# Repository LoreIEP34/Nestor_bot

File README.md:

# Nestor_bot
## Descripción:
Un robot controlado con esp32, que recibe señales bluetooth de un control de Playstation3 (Ps3), movilizado con motores dc que estan direccionados por un puente h, con 2 brazos hechos con servomotores que a traves de una garra improvisada puede sujetar objetos livianos y con un esp32 cam puede transmitir video a traves de wifi para poder ver lo a lo mismo que el robot ve.
##contenido del repositorio:
- /code: en esta carpeta  se puede encontrar el codigo para el funcionamiento del robot, en el cual se encuentra la deteccion del control Ps3 y la logica para el envio correcto de señales. El codigo fue diseñado y utilizado en arduino ide con lenguaje c.
- /hardware: en esta carpeta se podra encontrar el esquema y diseño de la pcb del robot hecho en la herraienta de diseño Kicad, en la version 8.0.
---
## Notas:
- El codigo para el funcionamiento del esp32 cam se puede conseguir facilmente en los ejemplos de esp32 en el arduino ide. Tambien se podria crear un codigo propio del funcionamiento para customizar el proyecto.
- Para poder tener mayor flexibilidad en el movimiento de la camara en la posicion mas conveninete simplemente conectamos de manera directa la placa principal con el esp32 cam con cables para alimentarlo.
- Para el ensamblaje y la presentacion final en este caso solo utilizamos carton prenzado con tornillos y poco mas, por esa razon no hay un diseño 3d del proyecto.
---
Este proyecto fue realizado como trabajo de aprendisaje escolar en la Tecnina N5 de Temperley, tambien conocida como "2 de abril" en Buenos Aires Argentina.

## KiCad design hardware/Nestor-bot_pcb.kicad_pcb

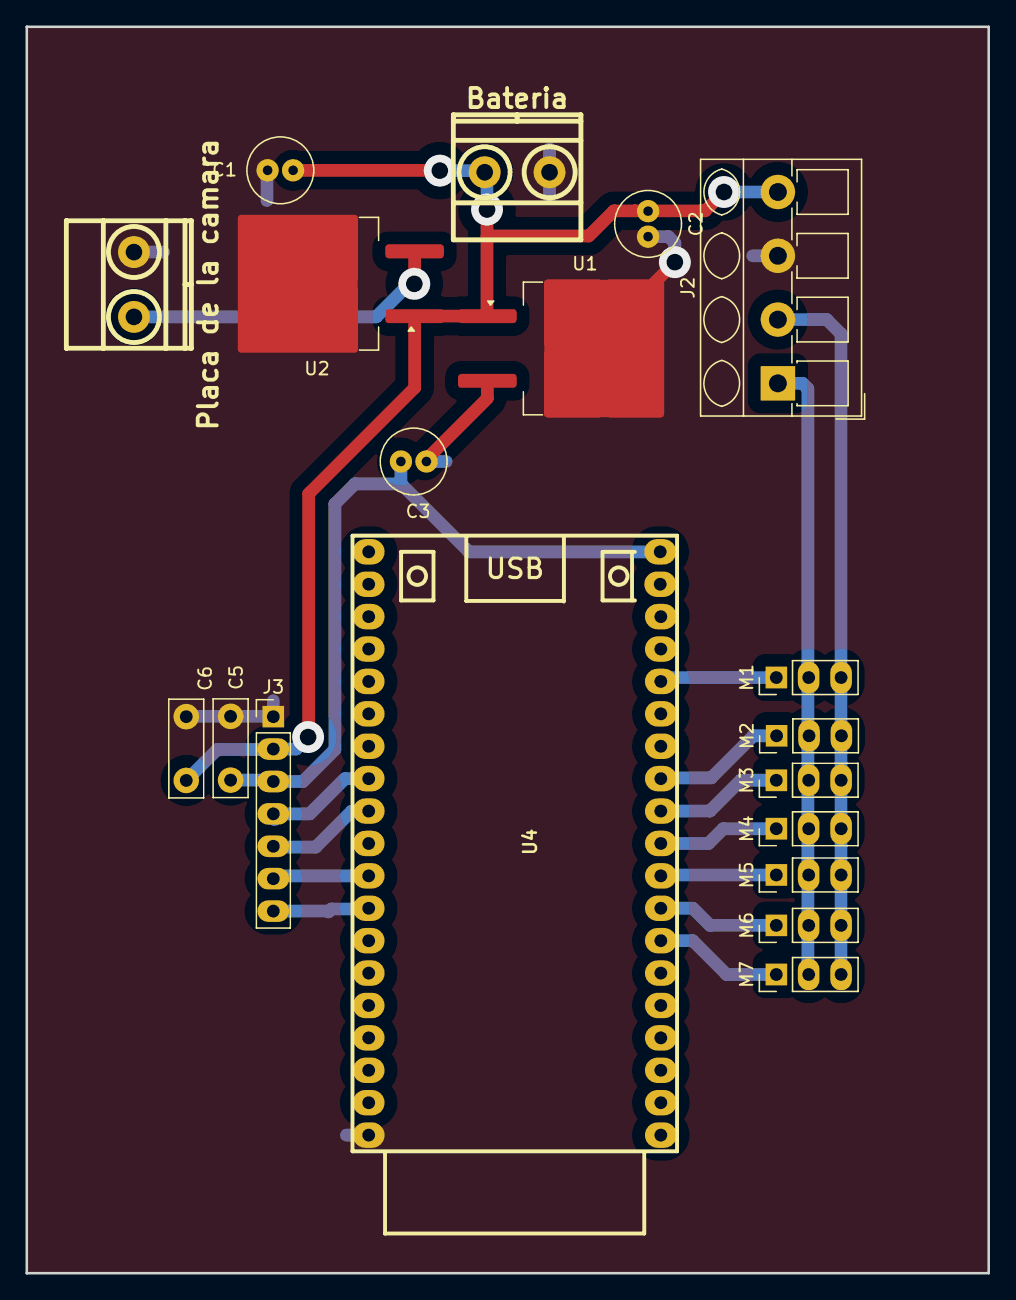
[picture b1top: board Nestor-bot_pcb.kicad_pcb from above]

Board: 2 copper layers, 75.4 x 97.7 mm, 19 parts (0 on the bottom side), 17 nets.

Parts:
C1, C2: 47u; C_Radial_D5.0mm_H5.0mm_P2.00mm
C3: 10u; C_Radial_D5.0mm_H5.0mm_P2.00mm
C5, C6: 100n; C_Disc_D7.5mm_W2.5mm_P5.00mm
J1: Bateria; BORNERA2
J2: stepdown lm2596; TerminalBlock_MetzConnect_Type205_RT04504UBLC_1x04_P5.00mm_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
J3: Puente h; PinHeader_1x07_P2.54mm_Vertical
J6: Placa de la camara; BORNERA2
M1, M2, M3, M4, M5, M6, M7: SG90; PinHeader_1x03_P2.54mm_Vertical
U1, U2: LM7805_TO220; TO-263-2
U4: ESP32-DEVKITC; ESP32_DEVKITC

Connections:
+5V: C3.2, C5.2, J3.3, U1.3 (VO), U4.19 (EXT_5V)
+5V(2): J6.1, U2.3 (VO)
+5V(3): J2.1, M1.2 (+), M2.2 (+), M3.2 (+), M4.2 (+), M5.2 (+), M6.2 (+), M7.2 (+)
+BATT: C1.1, C2.1, C6.2, J1.2, J2.4, J3.2, U1.1 (VI), U2.1 (VI)
/In1: J3.7, U4.31 (IO19)
/In2: J3.6, U4.30 (IO18)
/In3: J3.5, U4.28 (IO17)
/In4: J3.4, U4.27 (IO16)
/servo1: M1.1 (PWM), U4.15 (IO13)
/servo2: M2.1 (PWM), U4.12 (IO14)
/servo3: M3.1 (PWM), U4.11 (IO27)
/servo4: M4.1 (PWM), U4.10 (IO26)
/servo5: M5.1 (PWM), U4.9 (IO25)
/servo6: M6.1 (PWM), U4.8 (IO33)
/servo7: M7.1 (PWM), U4.7 (IO32)
GND: C1.2, C2.2, C3.1, C5.1, C6.1, J1.1, J2.3, J3.1, J6.2, U1.2 (GND), U2.2 (GND), U4.38 (GND3)
GND2: J2.2, M1.3 (-), M2.3 (-), M3.3 (-), M4.3 (-), M5.3 (-), M6.3 (-), M7.3 (-)

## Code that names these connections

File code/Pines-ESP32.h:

#define PIN_GPIO0 0  
#define PIN_GPIO1 1 
#define PIN_GPIO2 2  
#define PIN_GPIO3 3 
#define PIN_SERVO2 4 
#define PIN_GPIO5 5 
#define PIN_GPIO6 6 
#define PIN_GPIO7 7 
#define PIN_GPIO8 8 
#define PIN_GPIO9 9 
#define PIN_GPIO10 10 
#define PIN_GPIO11 11 
#define PIN_GPIO12 12  
#define PIN_SERVO1 13  
#define PIN_GPIO4 14 
#define PIN_GPIO15 15 
#define PIN_MdP1 16 
#define PIN_MdP2 17 
#define PIN_MiP1 18 
#define PIN_MiP2 19  
#define PIN_GPIO21 21 
#define PIN_GPIO22 22 
#define PIN_GPIO23 23  
#define PIN_SERVO3 25 
#define PIN_SERVO4 26 
#define PIN_SERVO5 27 
#define PIN_SERVO6 32 
#define PIN_SERVO7 33 
#define PIN_GPIO34 34  
#define PIN_GPIO35 35  
#define PIN_GPIO36 36  
#define PIN_GPIO39 39 
